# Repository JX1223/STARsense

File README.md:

View this project on [CADLAB.io](https://cadlab.io/project/23164). 

# STARsense

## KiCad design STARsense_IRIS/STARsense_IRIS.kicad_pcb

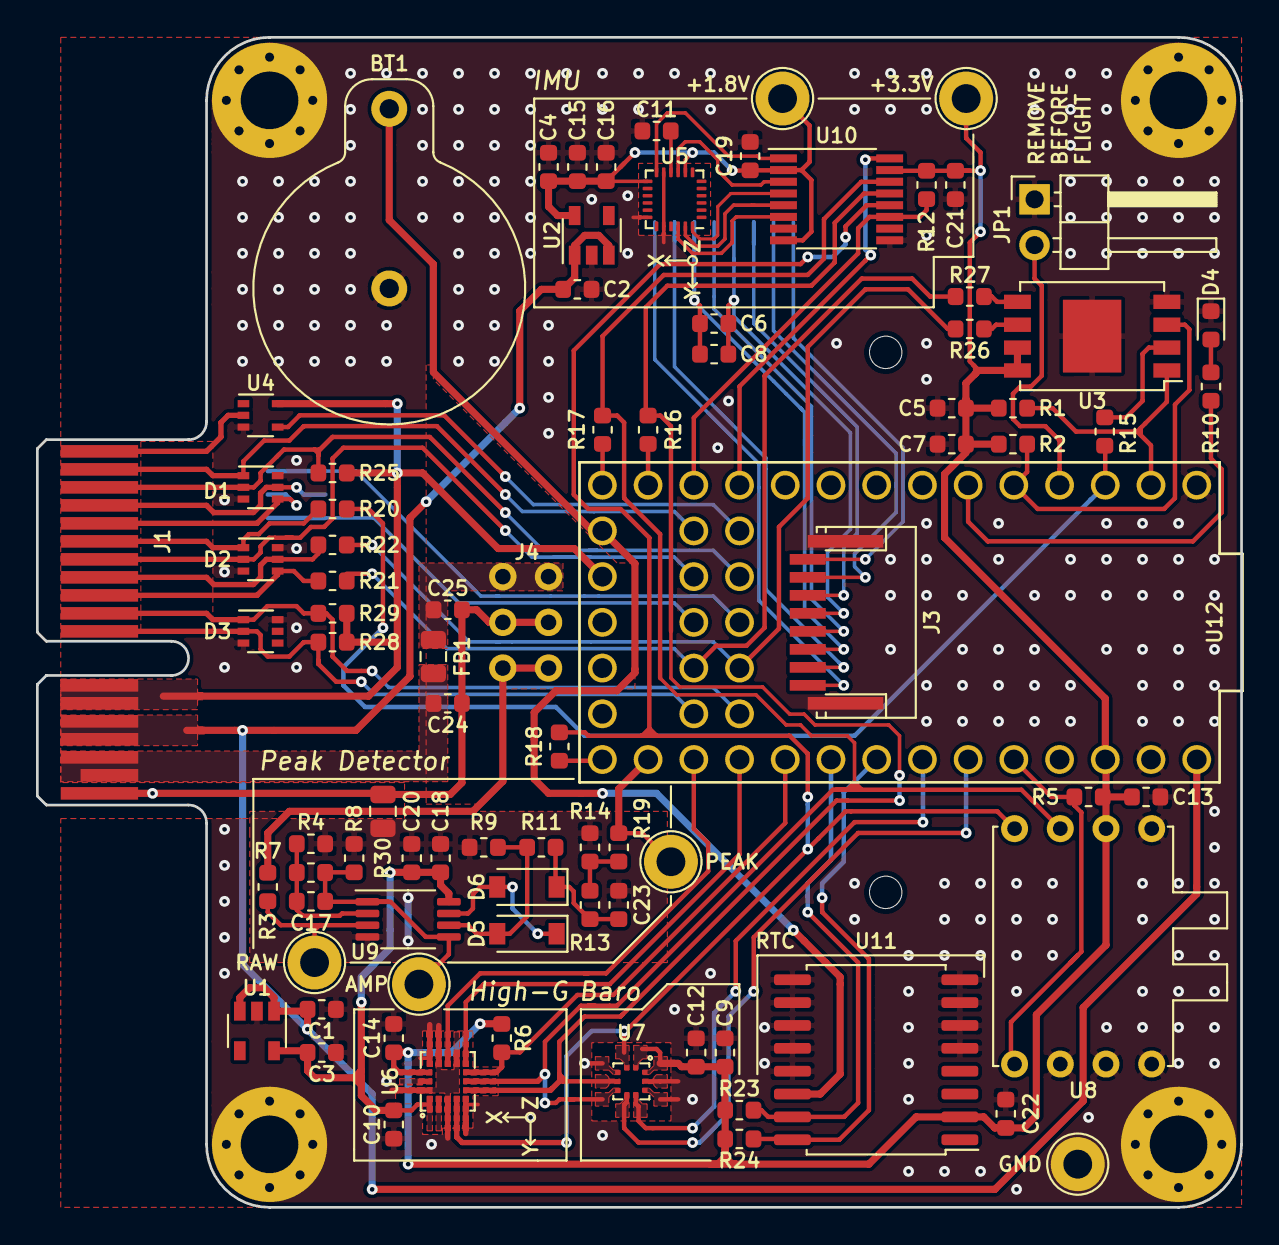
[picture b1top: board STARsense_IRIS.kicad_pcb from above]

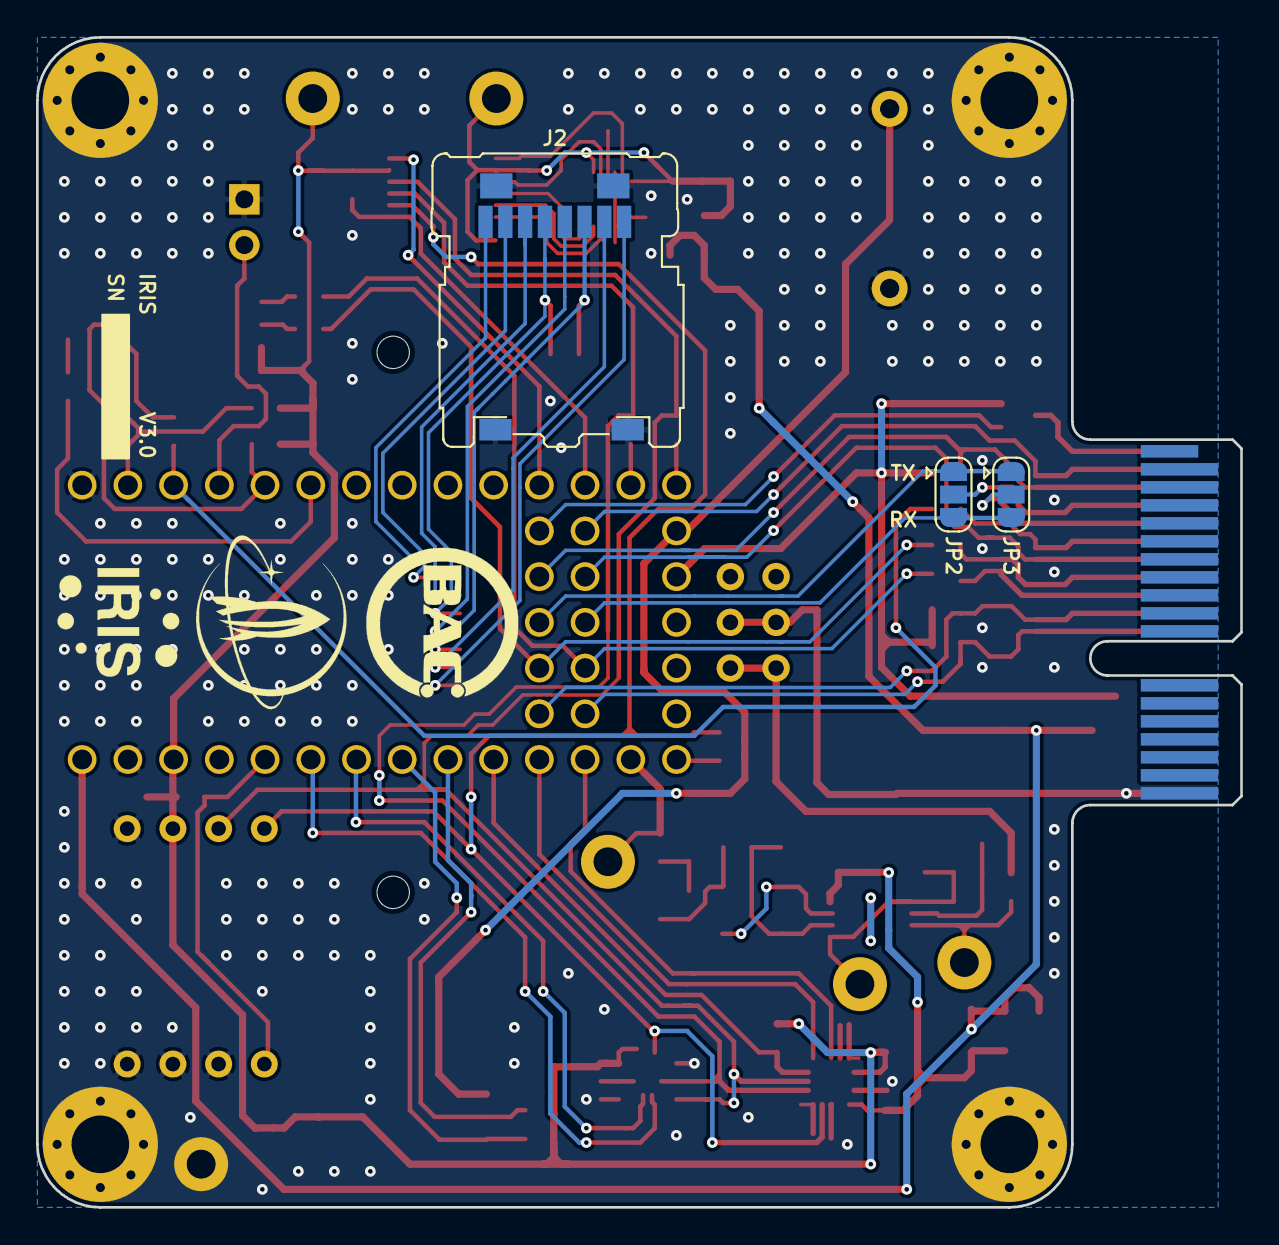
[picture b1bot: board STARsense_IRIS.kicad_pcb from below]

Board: 2 copper layers, 66.9 x 65.0 mm, 92 parts (3 on the bottom side), 73 nets.

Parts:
+1.8V, +3.3V: TestPoint_Probe; TestPoint_Loop_D2.60mm_Drill1.6mm_Beaded
AMP: TestPoint_Probe; TestPoint_Loop_D2.60mm_Drill1.6mm_Beaded
BT1: BH501
C1, C2, C3, C4, C7, C9, C13, C15, C22, C24: 1uF; C_0603_1608Metric
C5, C6, C10, C11, C12, C14, C16, C18, C19, C21, C25: 0.1uF; C_0603_1608Metric
C8, C20: 10uF; C_0603_1608Metric
C17: 10pF; C_0603_1608Metric
C23: 20nF; C_0603_1608Metric
D1, D2, D3: TPD4E1B06DCK; SOT-363_SC-70-6
D4: LTST-S270KRKT; LED_0603_1608Metric
D5, D6: MBR0540CT; D_SOD-123
FB1: 587-1919-1-ND; R_0805_2012Metric
GND: TestPoint_Probe; TestPoint_Loop_D2.60mm_Drill1.6mm_Beaded
H1, H2, H3, H4: M3; MountingHole_3.2mm_M3_Pad_Via
J1: PCIE1X; BUS_PCIexpress_x1
J2: ST1W008S4ER1500
J3: HFW8R-1STE1LF
J4: SiPM
JP1: Jumper; PinHeader_1x02_P2.54mm_Horizontal
JP2: TRX_Jumper1; SolderJumper-3_P1.3mm_Open_RoundedPad1.0x1.5mm
JP3: TRX_Jumper2; SolderJumper-3_P1.3mm_Open_RoundedPad1.0x1.5mm
PEAK: TestPoint_Probe; TestPoint_Loop_D2.60mm_Drill1.6mm_Beaded
R1, R2, R5, R6, R7, R8, R12, R25: 10k; R_0603_1608Metric
R3: 1k; R_0603_1608Metric
R4: 249R; R_0603_1608Metric
R9, R11: 100k; R_0603_1608Metric
R10: 130R; R_0603_1608Metric
R13, R15, R16, R17, R18, R19, R20, R21, R22, R26, R27: 0R; R_0603_1608Metric
R14: 24.9k; R_0603_1608Metric
R23, R24, R28, R29: 2.7k; R_0603_1608Metric
R30: 0R; R_0805_2012Metric
RAW: TestPoint_Probe; TestPoint_Loop_D2.60mm_Drill1.6mm_Beaded
U1: LP5907MFX-3.3; SOT-23-5
U2: LP5907MFX-1.8; SOT-23-5
U3: W25Q128JVEIQ
U4: SN74LV1T34DCK; SOT-353_SC-70-5
U5: ICM-20948; InvenSense_QFN-24_3x3mm_P0.4mm
U6: ADXL372
U7: BMP388
U8: HSCDRRN001BDSA3
U9: LT1807; MSOP-8_3x3mm_P0.65mm
U10: TXB0106PW; TSSOP-16_4.4x5mm_P0.65mm
U11: DS3231; SOIC-16W_7.5x10.3mm_P1.27mm
U12: Teensy4.0; Teensy40

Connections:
+1V8: +1.8V.1, C4.1, C15.1, C16.1, C19.1, U2.5, U5.8, U5.13, U10.2, U10.8
+3.3VA: C3.1, C10.1, C18.1, C20.1, U1.5, U6.1, U9.8
+3V3: +3.3V.1, C5.1, C7.1, C9.1, C12.1, C13.1, C14.1, C21.1, C22.1, J1.B12, J1.B13, R1.1, R2.1, R5.1, R6.1, R12.1, R23.2, R24.2, R25.2, R28.1, R29.1, U3.7, U3.8, U4.5, U6.14, U7.1, U7.10, U8.2, U10.15, U11.2, U12.16, U12.31
+5V: C1.1, C2.1, J1.B14, J1.B15, U1.1, U1.3, U2.1, U2.3, U12.33
+29.5V: C24.1, FB1.2, J1.B16, J1.B17
/CAP_STAT: D1.2, J1.B3, R25.1, U12.42
/CLK: J2.5, J3.4
/CMD: J2.3, J3.6
/CS_1V8: U5.22, U10.6
/CS_BARO: U7.6, U12.28
/CS_EX: D2.2, J1.B7, U12.41
/CS_HG: R6.2, U6.8, U12.24
/CS_IMU: R12.2, U10.11, U12.12
/CS_MEM: R1.2, U3.1, U12.2
/CS_PTOT: R5.2, U8.5, U12.29
/DAT0: J2.7, J3.2
/DAT1: J2.8, J3.1
/DAT2: J2.1, J3.8
/DAT3: J2.2, J3.7
/HG_INT1: U6.11, U12.22
/HG_INT2: U6.9, U12.23
/INT1: U10.16, U12.11
/INT1_1V8: U5.12, U10.1
/INT_BARO: U7.7, U12.27
/LED: R10.1, U12.6
/MISO: R17.2, U6.7, U7.5, U8.3, U10.14
/MISO1: R15.2, U3.2
/MISO1P: R15.1, R20.1, U12.3
/MISO_1V8: U5.9, U10.3
/MISO_EX: D2.1, J1.B6, R20.2
/MODE: JP1.2, U12.4
/MOSI: R16.2, U6.6, U7.4, U10.13
/MOSI1: R27.1, U3.5
/MOSI1P: R21.1, R27.2, U12.37
/MOSI_1V8: U5.24, U10.4
/MOSI_EX: D2.4, J1.B9, R21.2
/PWR_STAT: U4.4, U12.44
/PWR_STAT5V: J1.B1, U4.2
/RX1: JP2.3, JP3.3, U12.39
/SCL: R24.1, U11.16, U12.26
/SCLK: R18.2, U6.4, U7.2, U8.4, U10.12
/SCLK1: R26.1, U3.6
/SCLK1P: R22.1, R26.2, U12.38
/SCLK_1V8: U5.23, U10.5
/SCLK_EX: D2.5, J1.B8, R22.2
/SCL_EX: D3.2, J1.B11, R28.2, U12.35
/SDA: R23.1, U11.15, U12.25
/SDA_EX: D3.1, J1.B10, R29.2, U12.36
/SYNC: D1.1, J1.B2, U12.43
/SiPM_sig: J4.5, J4.6, R3.2
/TRX1: D1.5, J1.B4, JP2.2
/TRX2: D1.4, J1.B5, JP3.2
/TX1: JP2.1, JP3.1, U12.40
/VBAT: BT1.1, U11.14, U12.15
/VDD: C6.1, C8.1, J2.4, J3.5
/VSS: C6.2, C8.2, J2.6, J3.3
/WP: R2.2, U3.3, U12.5
/amp: AMP.1, C17.1, R7.1, R8.1, U9.1, U9.5
/peak: PEAK.1, R19.1, U12.21
/raw: R3.1, RAW.1, U9.3
GND: BT1.2, C1.2, C2.2, C3.2, C4.2, C5.2, C7.2, C9.2, C10.2, C11.2, C12.2, C13.2, C14.2, C15.2, C16.2, C19.2, C21.2, C22.2, C24.2, C25.2, D1.3, D1.6, D2.3, D2.6, D3.3, D3.6, D4.1, GND.1, H1.1, H2.1, H3.1, H4.1, J1.A18, J1.B18, J2.9, J3.MP, J4.3, J4.4, JP1.1, R30.2, U1.2, U2.2, U3.4, U3.9, U4.3, U5.11, U5.18, U5.20, U6.3, U6.5, U6.10, U6.12, U6.13, U6.16, U7.3, U7.8, U7.9, U8.1, U8.6, U8.7, U8.8, U10.9, U11.5, U11.6, U11.7, U11.8, U11.9, U11.10, U11.11, U11.12, U11.13, U12.1, U12.32
GNDA: C18.2, C20.2, C23.2, R4.2, R8.2, R9.2, R14.2, R30.1, U9.4
unnamed: C11.1, U5.10
unnamed: C17.2, R4.1, R7.2, U9.2
unnamed: C23.1, D6.1, R11.1, R13.2
unnamed: C25.1, FB1.1, J4.1, J4.2
unnamed: D4.2, R10.2
unnamed: D5.1, D6.2, U9.7
unnamed: D5.2, R9.1, R11.2, U9.6
unnamed: R13.1, R14.1, R19.2
unnamed: R16.1, U12.13
unnamed: R17.1, U12.14
unnamed: R18.1, U12.20

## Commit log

2020-08-02 Backlink to CADLAB.io has been added.
2020-08-02 Updated symbol organization
2020-08-02 Updated organization
2020-08-02 Fixing submodules
2020-08-02 readded submodules
2020-08-02 reset
2020-08-02 added digikey submodule
2020-08-02 Updated star power schematic
